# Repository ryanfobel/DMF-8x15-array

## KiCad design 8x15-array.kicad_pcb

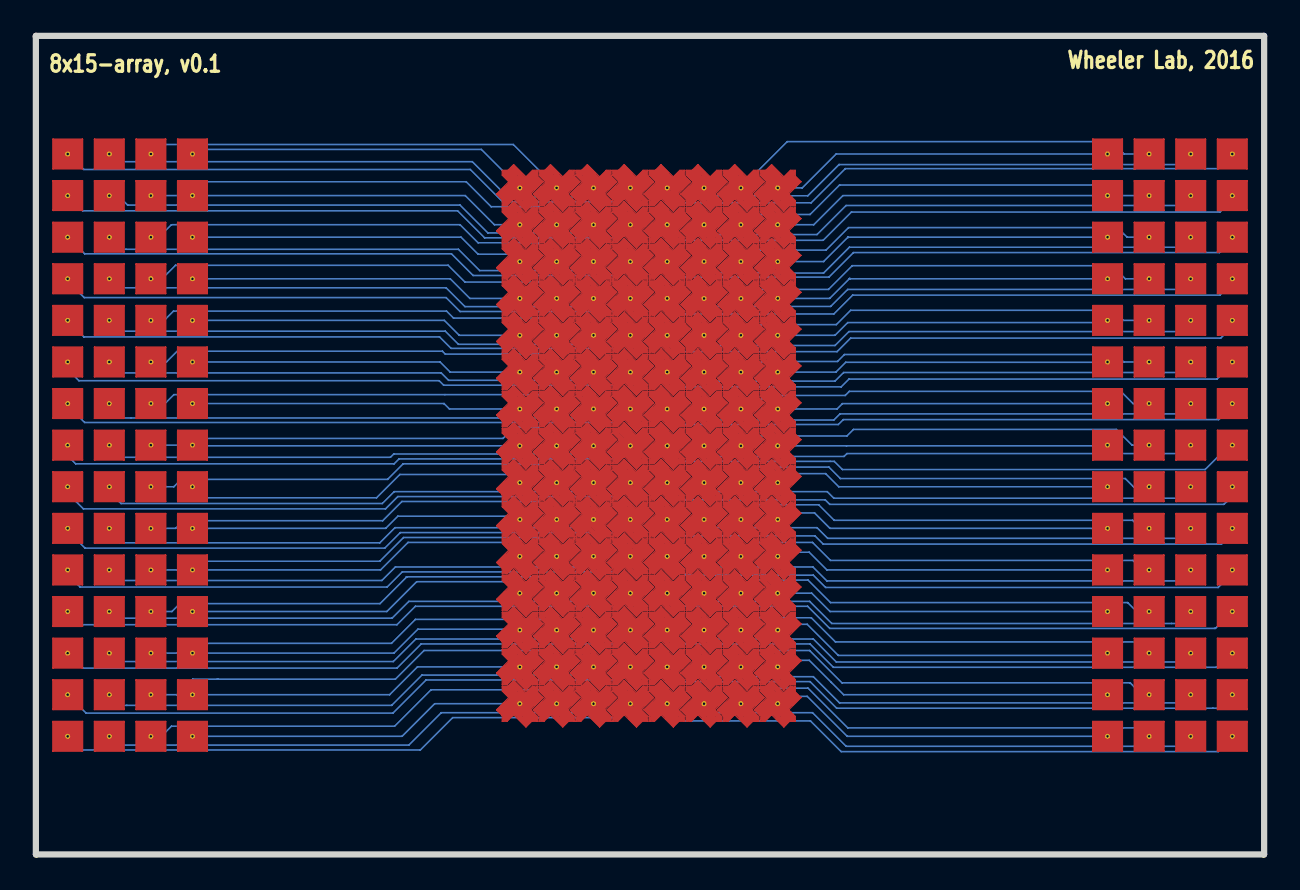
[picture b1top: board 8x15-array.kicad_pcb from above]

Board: 2 copper layers, 75.0 x 50.0 mm, 240 parts (0 on the bottom side), 120 nets.

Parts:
E0, E1, E2, E3, E4, E5, E6, E7, E8, E9, E10, E11, E12, E13, E14, E15, E16, E17, E18, E19, E20, E21, E22, E23, E24, E25, E26, E27, E28, E29, E30, E31, E32, E33, E34, E35, E36, E37, E38, E39, E40, E41, E42, E43, E44, E45, E46, E47, E48, E49, E50, E51, E52, E53, E54, E55, E56, E57, E58, E59, E60, E61, E62, E63, E64, E65, E66, E67, E68, E69, E70, E71, E72, E73, E74, E75, E76, E77, E78, E79, E80, E81, E82, E83, E84, E85, E86, E87, E88, E89, E90, E91, E92, E93, E94, E95, E96, E97, E98, E99, E100, E101, E102, E103, E104, E105, E106, E107, E108, E109, E110, E111, E112, E113, E114, E115, E116, E117, E118, E119: CONN_01X01; 2.25mm_25um-gap_2-teeth
P1, P2, P3, P4, P5, P6, P7, P8, P9, P10, P11, P12, P13, P14, P15, P16, P17, P18, P19, P20, P21, P22, P23, P24, P25, P26, P27, P28, P29, P30, P31, P32, P33, P34, P35, P36, P37, P38, P39, P40, P41, P42, P43, P44, P45, P46, P47, P48, P49, P50, P51, P52, P53, P54, P55, P56, P57, P58, P59, P60, P61, P62, P63, P64, P65, P66, P67, P68, P69, P70, P71, P72, P73, P74, P75, P76, P77, P78, P79, P80, P81, P82, P83, P84, P85, P86, P87, P88, P89, P90, P91, P92, P93, P94, P95, P96, P97, P98, P99, P100, P101, P102, P103, P104, P105, P106, P107, P108, P109, P110, P111, P112, P113, P114, P115, P116, P117, P118, P119, P120: CONN_01X01; 1.9mm_DMF_Electrode-hole

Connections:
unnamed: E0.1, P1.1
unnamed: E1.1, P2.1
unnamed: E2.1, P3.1
unnamed: E3.1, P4.1
unnamed: E4.1, P5.1
unnamed: E5.1, P6.1
unnamed: E6.1, P7.1
unnamed: E7.1, P8.1
unnamed: E8.1, P9.1
unnamed: E9.1, P10.1
unnamed: E10.1, P11.1
unnamed: E11.1, P12.1
unnamed: E12.1, P13.1
unnamed: E13.1, P14.1
unnamed: E14.1, P15.1
unnamed: E15.1, P16.1
unnamed: E16.1, P17.1
unnamed: E17.1, P18.1
unnamed: E18.1, P19.1
unnamed: E19.1, P20.1
unnamed: E20.1, P21.1
unnamed: E21.1, P22.1
unnamed: E22.1, P23.1
unnamed: E23.1, P24.1
unnamed: E24.1, P25.1
unnamed: E25.1, P26.1
unnamed: E26.1, P27.1
unnamed: E27.1, P28.1
unnamed: E28.1, P29.1
unnamed: E29.1, P30.1
unnamed: E30.1, P31.1
unnamed: E31.1, P32.1
unnamed: E32.1, P33.1
unnamed: E33.1, P34.1
unnamed: E34.1, P35.1
unnamed: E35.1, P36.1
unnamed: E36.1, P37.1
unnamed: E37.1, P38.1
unnamed: E38.1, P39.1
unnamed: E39.1, P40.1
unnamed: E40.1, P41.1
unnamed: E41.1, P42.1
unnamed: E42.1, P43.1
unnamed: E43.1, P44.1
unnamed: E44.1, P45.1
unnamed: E45.1, P46.1
unnamed: E46.1, P47.1
unnamed: E47.1, P48.1
unnamed: E48.1, P49.1
unnamed: E49.1, P50.1
unnamed: E50.1, P51.1
unnamed: E51.1, P52.1
unnamed: E52.1, P53.1
unnamed: E53.1, P54.1
unnamed: E54.1, P55.1
unnamed: E55.1, P56.1
unnamed: E56.1, P57.1
unnamed: E57.1, P58.1
unnamed: E58.1, P59.1
unnamed: E59.1, P60.1
unnamed: E60.1, P61.1
unnamed: E61.1, P62.1
unnamed: E62.1, P63.1
unnamed: E63.1, P64.1
unnamed: E64.1, P65.1
unnamed: E65.1, P66.1
unnamed: E66.1, P67.1
unnamed: E67.1, P68.1
unnamed: E68.1, P69.1
unnamed: E69.1, P70.1
unnamed: E70.1, P71.1
unnamed: E71.1, P72.1
unnamed: E72.1, P73.1
unnamed: E73.1, P74.1
unnamed: E74.1, P75.1
unnamed: E75.1, P76.1
unnamed: E76.1, P77.1
unnamed: E77.1, P78.1
unnamed: E78.1, P79.1
unnamed: E79.1, P80.1
unnamed: E80.1, P81.1
unnamed: E81.1, P82.1
unnamed: E82.1, P83.1
unnamed: E83.1, P84.1
unnamed: E84.1, P85.1
unnamed: E85.1, P86.1
unnamed: E86.1, P87.1
unnamed: E87.1, P88.1
unnamed: E88.1, P89.1
unnamed: E89.1, P90.1
unnamed: E90.1, P91.1
unnamed: E91.1, P92.1
unnamed: E92.1, P93.1
unnamed: E93.1, P94.1
unnamed: E94.1, P95.1
unnamed: E95.1, P96.1
unnamed: E96.1, P97.1
unnamed: E97.1, P98.1
unnamed: E98.1, P99.1
unnamed: E99.1, P100.1
unnamed: E100.1, P101.1
unnamed: E101.1, P102.1
unnamed: E102.1, P103.1
unnamed: E103.1, P104.1
unnamed: E104.1, P105.1
unnamed: E105.1, P106.1
unnamed: E106.1, P107.1
unnamed: E107.1, P108.1
unnamed: E108.1, P109.1
unnamed: E109.1, P110.1
unnamed: E110.1, P111.1
unnamed: E111.1, P112.1
unnamed: E112.1, P113.1
unnamed: E113.1, P114.1
unnamed: E114.1, P115.1
unnamed: E115.1, P116.1
unnamed: E116.1, P117.1
unnamed: E117.1, P118.1
unnamed: E118.1, P119.1
unnamed: E119.1, P120.1

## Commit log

2016-11-30 Finish making connections
2016-11-30 Update to use through-hole contact pads
2016-11-30 Adjust front soldermask
